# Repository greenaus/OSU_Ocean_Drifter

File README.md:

# OSU_Ocean_Drifter
The code repo for the HC 407 ocean drifter dev-kit

## ArudinoGPS.ino Dependencies:

Adafruit Unified Sensor  
Adafruit Circuit Playground  
Adafruit MAX31856 Library  
DHT sensor library  
Tiny GPS

## Current Arduino Pinout
### DHT Humidity Sensor:
plus  -> 5V

out   -> D2

minus -> GND

### GPS
VCC -> 5V  (Needs external source. Arudino can't provide enough power to run!)

RX  -> D3

TX  -> D4

GND -> GND

### Max31856 Thermocouple:
Vin -> 5V

GND -> GND

SCK -> D13

SDO -> D12

SDI -> D11

CS  -> D10

### SD Card (Tentative):
CS   -> D9

SCK  -> D13

MOSI -> D11

MISO -> D12

VCC  -> 5V

GND  -> GND

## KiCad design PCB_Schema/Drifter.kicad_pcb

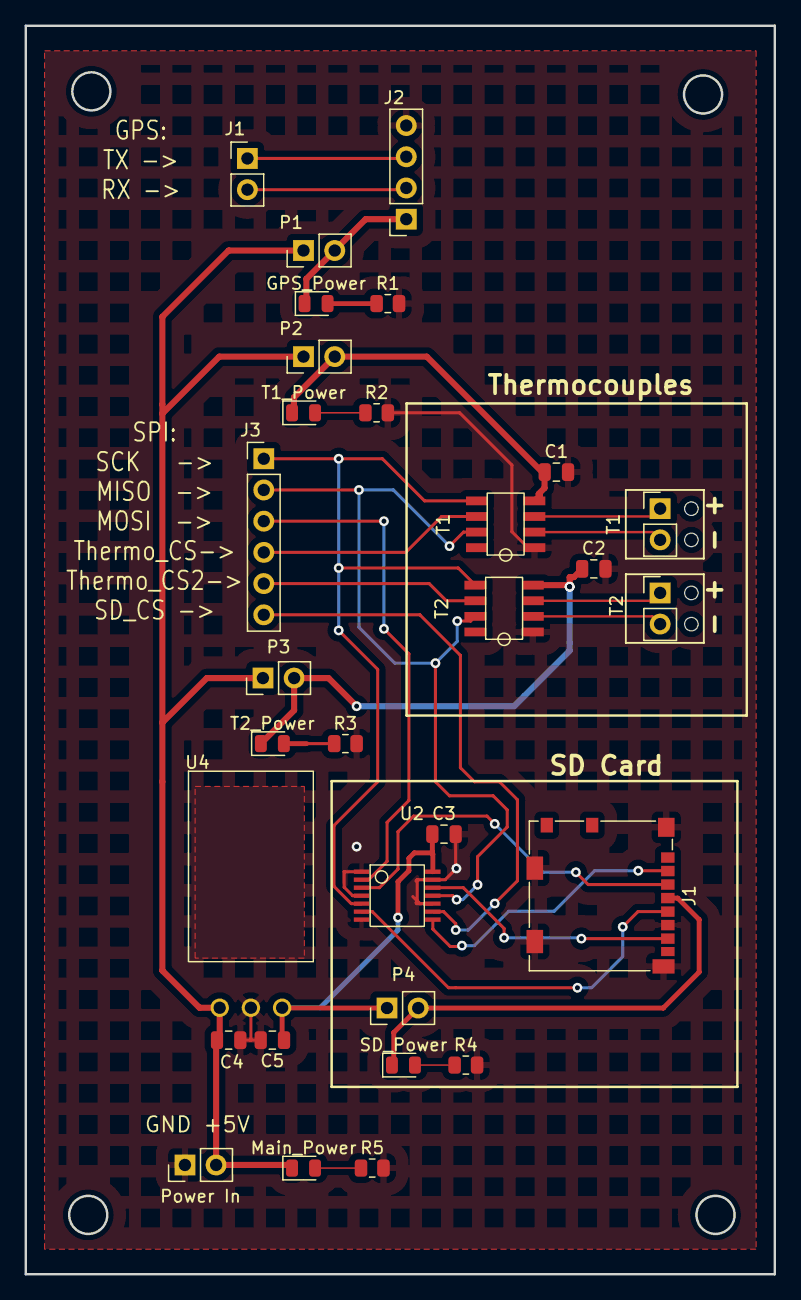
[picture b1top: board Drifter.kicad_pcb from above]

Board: 2 copper layers, 61.0 x 101.6 mm, 30 parts (0 on the bottom side), 19 nets.

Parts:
C1, C2, C3, C4, C5: C_0805_2012Metric
GPS_Power: LED_0805_2012Metric
J1: microSD_HC_Molex_104031-0811
J1#2: PinHeader_1x02_P2.54mm_Vertical
J2: PinSocket_1x04_P2.54mm_Vertical
J3: PinHeader_1x06_P2.54mm_Vertical
Main_Power: LED_0805_2012Metric
P1, P2, P3, P4: PinHeader_1x02_P2.54mm_Vertical
Power In: PinHeader_1x02_P2.54mm_Vertical
R1, R2, R3, R4, R5: R_0805_2012Metric
SD_Power: LED_0805_2012Metric
T1, T2#2: PinHeader_1x02_P2.54mm_Vertical
T1#2, T2: Max6675
T1_Power, T2_Power: LED_0805_2012Metric
U2: 74VHC125
U4: LM3940

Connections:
+3.3V: C3.1, C5.1, J1.4, P4.1, P4.2, SD_Power.1, U2.14, U4.3
+5V: C1.1, C2.1, C4.1, GPS_Power.1, J2.1, Main_Power.1, P1.1, P1.2, P2.1, P2.2, P3.1, P3.2, Power In.2, T1#2.4, T1_Power.1, T2.4, T2_Power.1, U4.1
/CS_SD: J3.6, U2.9
/CS_Thermo: J3.4, T1#2.6
/MISO: J3.2, T1#2.7, T2.7, U2.11
/MOSI: J3.3, U2.2
/SCK: J3.1, T1#2.5, T2.5, U2.5
CD: J1.2, U2.8
CLK: J1.5, U2.6
CMD: J1.3, U2.3
CS_Thermo2: J3.5, T2.6
DAT0: J1.7, U2.12
GND: C1.2, C2.2, C3.2, C4.2, C5.2, J1.6, J1.11, J2.4, Power In.1, R1.2, R2.2, R3.2, R4.2, R5.2, T1#2.1, T2.1, U2.1, U2.4, U2.7, U2.10, U2.13, U4.2
RX: J1#2.2, J2.2
T2+: T2.3, T2#2.1
T2-: T2.2, T2#2.2
T+: T1.1, T1#2.3
T-: T1.2, T1#2.2
TX: J1#2.1, J2.3

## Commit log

2022-04-05 Added Initial Arduino Code
2022-04-05 Updated ReadMe with Arduino Library dependencies
2022-04-05 Updated README formatting
2022-04-12 Added Sensor Pinouts
2022-04-12 Fixed Formatting
2022-04-19 Updated Main Program
    Added SD libraries
2022-04-23 Create DS_Ref
2022-04-23 Added Max6675 (Thermocouple) DS
2022-04-23 Added 5-3.3 Reg & SD SPI Buffer DS
2022-04-23 Rename DS_Ref to DS_Ref.md
2022-04-23 Update DS_Ref.md Formatting
2022-04-26 Create Filler
2022-04-26 Footprints
2022-05-01 Updated library dependencies
2022-05-02 Updated KiCad PCB/Schema files
2022-05-02 Updated custom Footprints
2022-07-21 Updated PCB
2022-09-11 Updated PCB and Schematic files
2022-09-11 Basic Project BOM
2022-09-13 Uploaded GPS tutorial prototype
